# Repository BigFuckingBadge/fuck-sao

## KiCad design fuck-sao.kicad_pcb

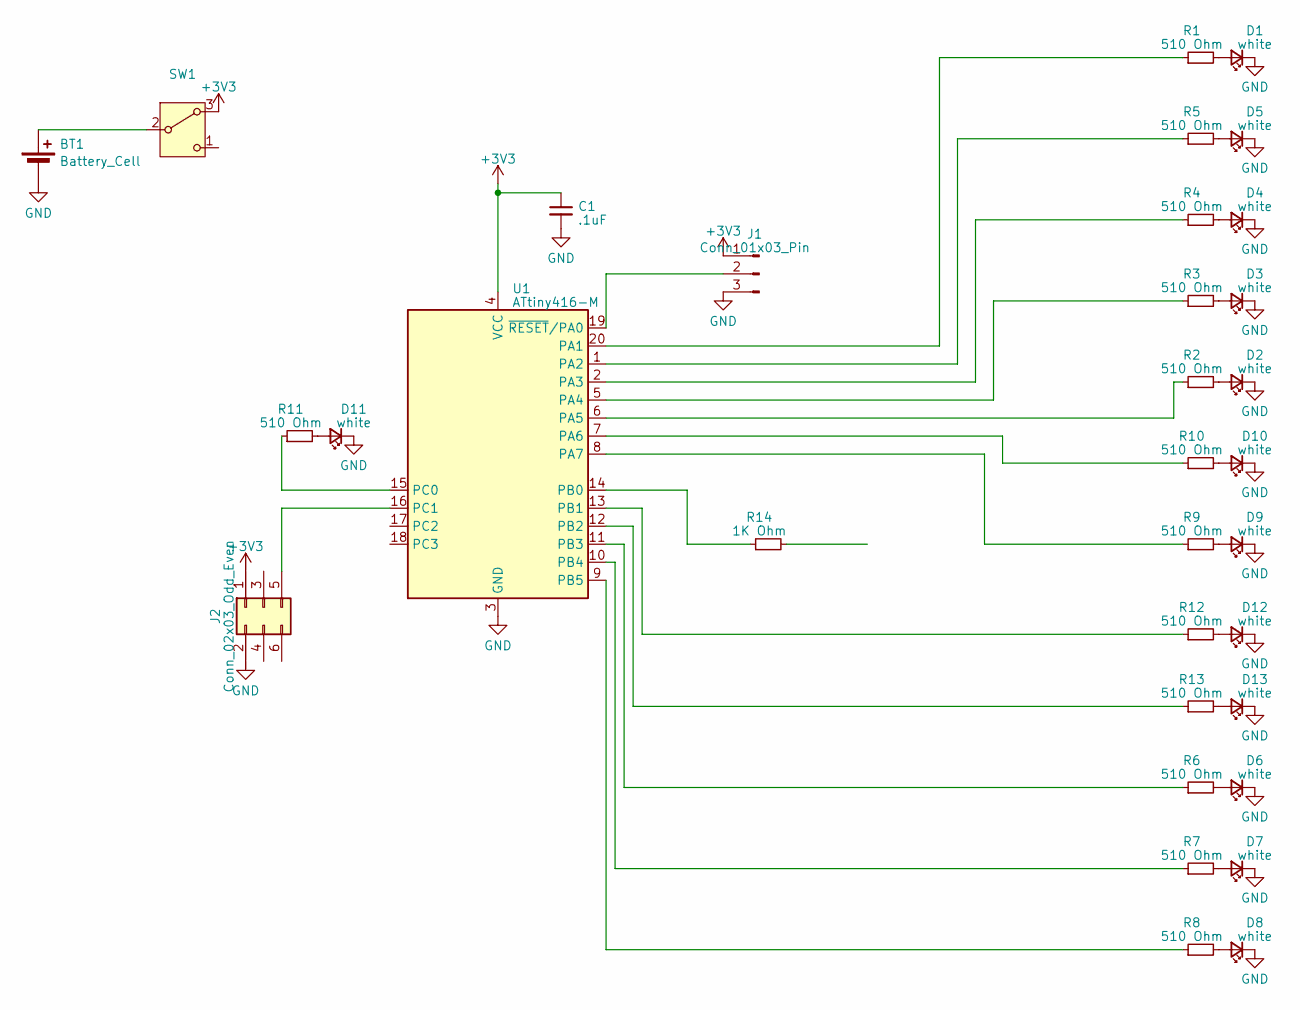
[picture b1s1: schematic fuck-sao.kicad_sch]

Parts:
BT1: Battery_Cell
C1: .1uF; C_0603_1608Metric
D1, D2, D3, D4, D5, D6, D7, D8, D9, D10, D11, D12, D13: white; LED_0603_1608Metric
J1: Conn_01x03_Pin; PinHeader_1x03_P2.54mm_Vertical
J2: Conn_02x03_Odd_Even; PinHeader_2x03_P2.54mm_Vertical
R1, R2, R3, R4, R5, R6, R7, R8, R9, R10, R11, R12, R13: 510 Ohm; R_0603_1608Metric
R14: 1K Ohm; R_0603_1608Metric
SW1: SW_Nidec_CAS-120A1; Nidec_Copal_CAS-120A
U1: ATtiny416-M; VQFN-20-1EP_3x3mm_P0.4mm_EP1.7x1.7mm

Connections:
+3V3: C1.1, J1.1, J2.1, SW1.3 (A), U1.4 (VCC)
GND: BT1.2 (-), C1.2, D1.1 (K), D2.1 (K), D3.1 (K), D4.1 (K), D5.1 (K), D6.1 (K), D7.1 (K), D8.1 (K), D9.1 (K), D10.1 (K), D11.1 (K), D12.1 (K), D13.1 (K), J1.3, J2.2, U1.3 (GND), U1.21 (GND)
unnamed: BT1.1 (+), BT1.3, SW1.2 (B)
unnamed: D1.2 (A), R1.2
unnamed: D2.2 (A), R2.2
unnamed: D3.2 (A), R3.2
unnamed: D4.2 (A), R4.2
unnamed: D5.2 (A), R5.2
unnamed: D6.2 (A), R6.2
unnamed: D7.2 (A), R7.2
unnamed: D8.2 (A), R8.2
unnamed: D9.2 (A), R9.2
unnamed: D10.2 (A), R10.2
unnamed: D11.2 (A), R11.2
unnamed: D12.2 (A), R12.2
unnamed: D13.2 (A), R13.2
unnamed: J1.2, U1.19 (~RESET/PA0)
unnamed: J2.5, U1.16 (PC1)
unnamed: R1.1, U1.20 (PA1)
unnamed: R5.1, U1.1 (PA2)
unnamed: R4.1, U1.2 (PA3)
unnamed: R3.1, U1.5 (PA4)
unnamed: R2.1, U1.6 (PA5)
unnamed: R10.1, U1.7 (PA6)
unnamed: R9.1, U1.8 (PA7)
unnamed: R14.1, U1.14 (PB0)
unnamed: R12.1, U1.13 (PB1)
unnamed: R13.1, U1.12 (PB2)
unnamed: R6.1, U1.11 (PB3)
unnamed: R7.1, U1.10 (PB4)
unnamed: R8.1, U1.9 (PB5)
unnamed: R11.1, U1.15 (PC0)

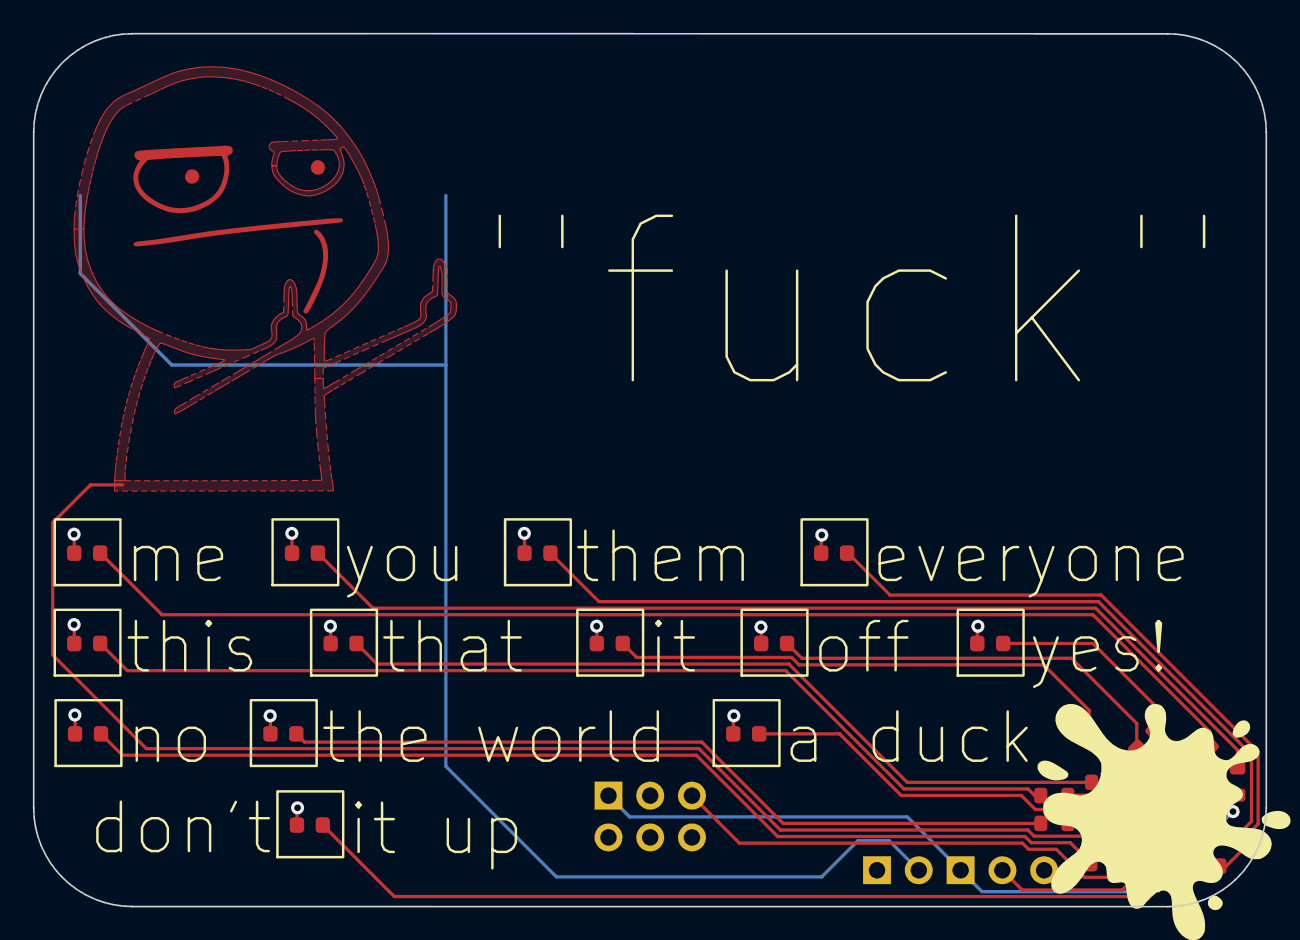
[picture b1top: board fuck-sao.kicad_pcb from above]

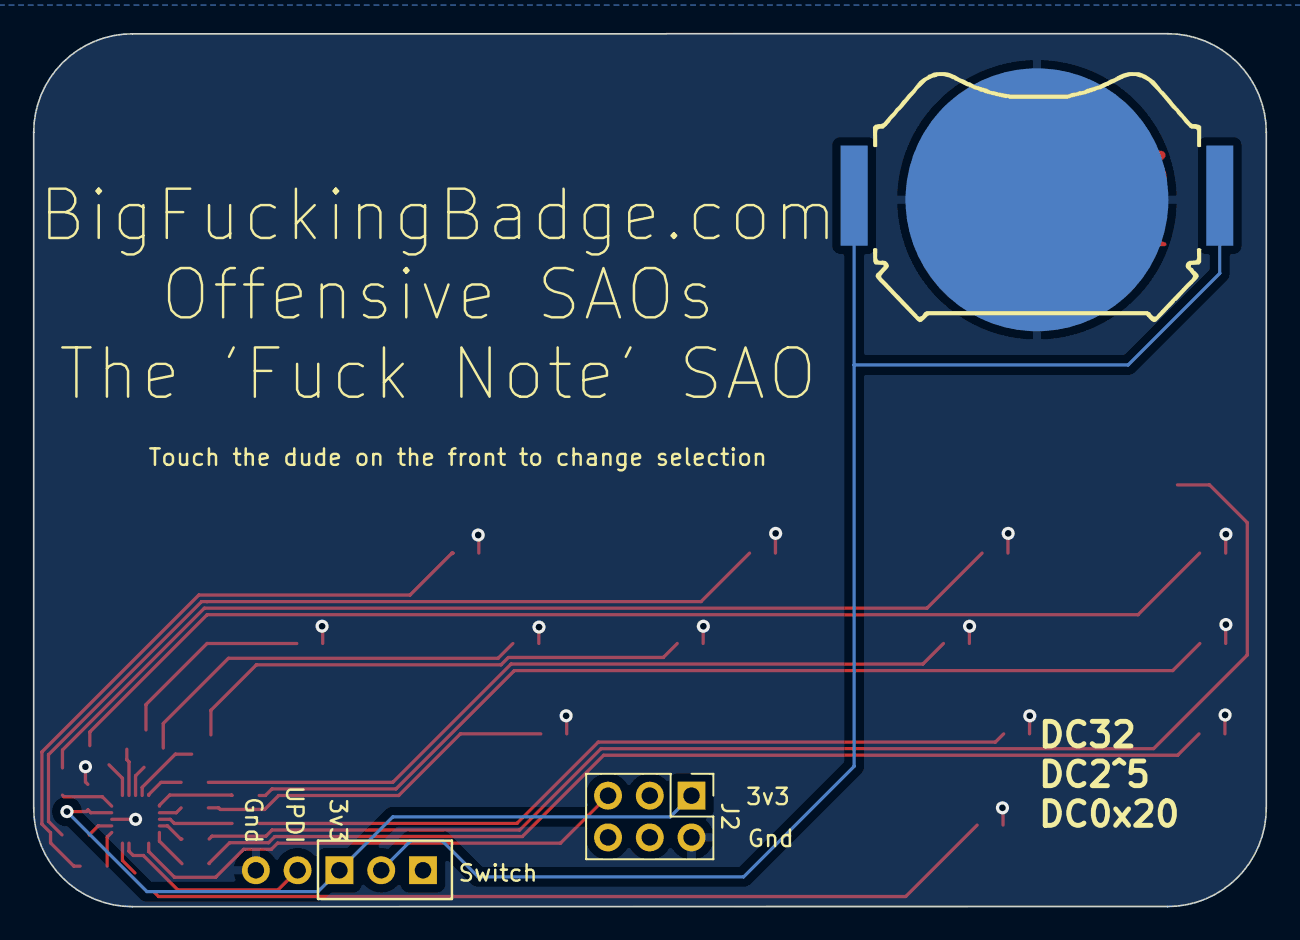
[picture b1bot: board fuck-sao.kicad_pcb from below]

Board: 2 copper layers, 75.0 x 53.1 mm, 33 parts (2 on the bottom side), 32 nets.

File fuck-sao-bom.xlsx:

Designator | Comment | JLCPCB Part #（optional） | Footprint
C1 | .1uF |  | Capacitor_SMD:C_0603_1608Metric
D1, D2, D3, D4, D5, D6, D7, D8, D9, D10, D11, D12, D13 | white | C2760787 | LED_SMD:LED_0603_1608Metric
R1, R2, R3, R4, R5, R6, R7, R8, R9, R10, R11, R12, R13 | 510 Ohm |  | Resistor_SMD:R_0603_1608Metric
R14 | 1K Ohm |  | Resistor_SMD:R_0603_1608Metric
U1 | ATtiny416-M | C507118 | Package_DFN_QFN:VQFN-20-1EP_3x3mm_P0.4mm_EP1.7x1.7mm

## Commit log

2024-02-13 code finished
2024-02-13 added comments
2024-04-01 new touch program and new board desigh
2024-04-01 PCB rules addressed
2024-07-04 media and more
